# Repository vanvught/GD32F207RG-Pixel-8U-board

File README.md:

# GD32F207RG Pixel 8U board

https://www.gd32-dmx.org

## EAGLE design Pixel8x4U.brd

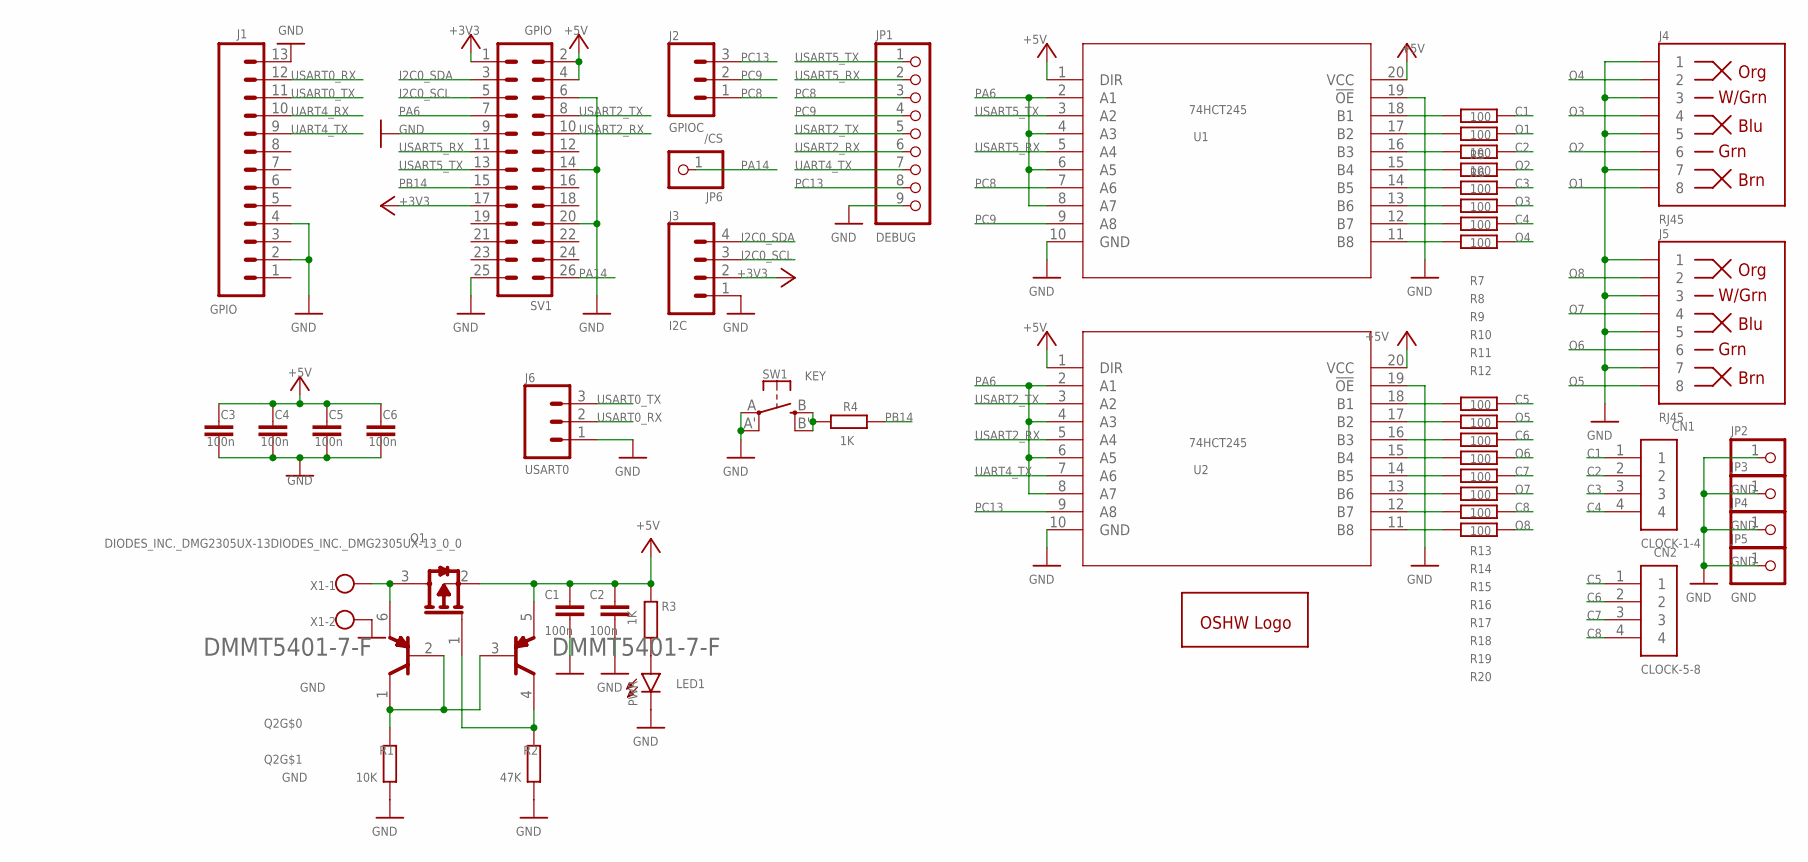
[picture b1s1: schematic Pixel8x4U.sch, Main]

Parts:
C1, C2, C3, C4, C5, C6: 100n; C0603
CN1: CLOCK-1-4; 1X04-CLEANBIG
CN2: CLOCK-5-8; 1X04-CLEANBIG
GOLD_ORB_SM1: OSHWLOGOLOGO5MM; OSHW_5MM
J1: GPIO; 1X13
J2: GPIOC; 1X03
J3: I2C; 1X04
J4, J5: RJ45; RJ45-8
J6: USART0; 1X03
JP1: DEBUG; 1X09
JP2, JP3, JP4, JP5: GND; 1X01-CLEANBIG
JP6: /CS; 1X01-CLEANBIG
LED1: PWR; CHIP-LED0603
Q1: DIODES_INC._DMG2305UX-13DIODES_INC._DMG2305UX-13_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; DIODES_INC._DMG2305UX-13_0
Q2: DMMT5401-7-F_0_0; DIODES_DMMT5401-7-F_0
R1: 10K; R0402
R2: 47K; R0402
R3, R4: 1K; R0402
R5, R6, R7, R8, R9, R10, R11, R12, R13, R14, R15, R16, R17, R18, R19, R20: 100; R0402
SV1: GPIO; MA13-2
SW1: KEY; EVQ-Q2
U1, U2: 74HCT245; PW20
X1: W237-102

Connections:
+3V3: J3.2, SV1.1, SV1.17
+5V: C1.1, C2.1, C3.1, C4.1, C5.1, C6.1, Q1.2 (S), Q2.5 (E2), R3.1, SV1.2, SV1.4, U1.1 (DIR), U1.20 (VCC), U2.1 (DIR), U2.20 (VCC)
C1: CN1.1, R5.2
C2: CN1.2, R7.2
C3: CN1.3, R9.2
C4: CN1.4, R11.2
C5: CN2.1, R13.2
C6: CN2.2, R15.2
C7: CN2.3, R17.2
C8: CN2.4, R19.2
GND: C1.2, C2.2, C3.2, C4.2, C5.2, C6.2, J1.2, J1.4, J1.13, J3.1, J4.1, J4.3, J4.5, J4.7, J5.1, J5.3, J5.5, J5.7, J6.1, JP1.9, JP2.1, JP3.1, JP4.1, JP5.1, LED1.C, R1.1, R2.1, SV1.6, SV1.9, SV1.14, SV1.20, SV1.25, SW1.A, SW1.A' (P1), U1.10 (GND), U1.19 (!OE), U2.10 (GND), U2.19 (!OE), X1.2
I2C0_SCL: J3.3, SV1.5
I2C0_SDA: J3.4, SV1.3
unnamed: Q2.1 (C1), Q2.2 (B1), Q2.3 (B2), R1.2
unnamed: Q1.3 (D), Q2.6 (E1), X1.1
unnamed: Q1.1 (G), Q2.4 (C2), R2.2
unnamed: R4.1, SW1.B (S), SW1.B' (S1)
unnamed: R6.1, U1.17 (B2)
unnamed: R12.1, U1.11 (B8)
unnamed: R10.1, U1.13 (B6)
unnamed: R8.1, U1.15 (B4)
unnamed: R5.1, U1.18 (B1)
unnamed: R7.1, U1.16 (B3)
unnamed: R14.1, U2.17 (B2)
unnamed: R16.1, U2.15 (B4)
unnamed: R18.1, U2.13 (B6)
unnamed: LED1.A, R3.2
unnamed: R20.1, U2.11 (B8)
unnamed: R9.1, U1.14 (B5)
unnamed: R11.1, U1.12 (B7)
unnamed: R13.1, U2.18 (B1)
unnamed: R15.1, U2.16 (B3)
unnamed: R17.1, U2.14 (B5)
unnamed: R19.1, U2.12 (B7)
O1: J4.8, R6.2
O2: J4.6, R8.2
O3: J4.4, R10.2
O4: J4.2, R12.2
O5: J5.8, R14.2
O6: J5.6, R16.2
O7: J5.4, R18.2
O8: J5.2, R20.2
PA6: SV1.7, U1.2 (A1), U1.4 (A3), U1.6 (A5), U1.8 (A7), U2.2 (A1), U2.4 (A3), U2.6 (A5), U2.8 (A7)
PA14: JP6.1, SV1.26
PB14: R4.2, SV1.15
PC8: J2.1, JP1.3, U1.7 (A6)
PC9: J2.2, JP1.4, U1.9 (A8)
PC13: J2.3, JP1.8, U2.9 (A8)
UART4_RX: J1.10
UART4_TX: J1.9, JP1.7, U2.7 (A6)
USART0_RX: J1.12, J6.2
USART0_TX: J1.11, J6.3
USART2_RX: JP1.6, SV1.10, U2.5 (A4)
USART2_TX: JP1.5, SV1.8, U2.3 (A2)
USART5_RX: JP1.2, SV1.11, U1.5 (A4)
USART5_TX: JP1.1, SV1.13, U1.3 (A2)

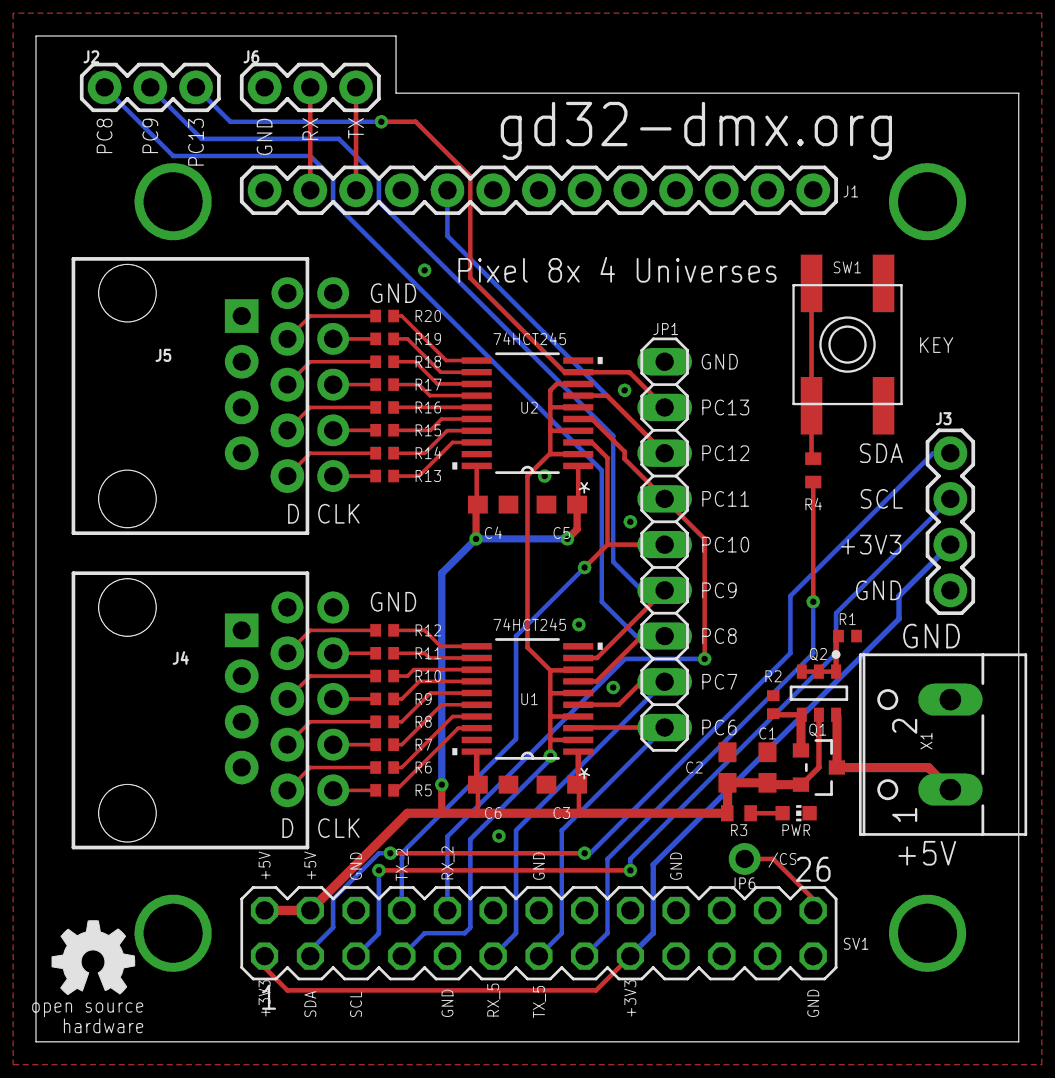
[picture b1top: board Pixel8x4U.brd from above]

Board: 2 copper layers, 54.6 x 55.9 mm, 49 parts (0 on the bottom side), 55 nets.

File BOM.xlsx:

Qty | Designator | Footprint | Comment | LCSC Part #
6 | C1, C2, C3, C4, C5, C6 | C0603 | 100n | C14663
1 | LED1 | CHIP-LED0603 | PWR | C2286
1 | Q1 | SOT-23-3 | DMG2305UX | C150470
1 | Q2 | SOT-23-6L | DMMT5401-7-F_0_0 | C154733
1 | R1 | R0402 | 10K | C25744
1 | R2 | R0402 | 47K | C25792
2 | R3, R4 | R0402 | 1K | C11702
16 | R5, R6, R7, R8, R9, R10, R11, R12, R13, R14, R15, R16, R17, R18, R19, R20 | R0402 | 100 | C25076
1 | SW1 | EVQ-Q2 | SPST 6*6mm Tactile Switch | C221880
2 | U1, U2 | SSOP-20 | 74HCT245 | C10910
32

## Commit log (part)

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2025-01-19 Added Eagle files, BOM and CPL

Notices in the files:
parts and their libraries:
SparkFun-Connectors: Licensing: Creative Commons ShareAlike 4.0 International - https://creativecommons.org/licenses/by-sa/4.0
